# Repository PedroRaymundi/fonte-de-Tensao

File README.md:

# Fonte de Tensão
O objetivo final desse projeto é criar uma fonte de tensão com uma entrada de 127V AC 
e saída variável entre 3V e 12V com corrente contínua e 100mA

## Materiais
Materiais|Especificações|Preço
---------|--------------|-----
Transformador|16V 1A|+-R$50
Potenciômetro|2KΩ|+-R$1,04
Diodo (4x)|400V 3A|+-R$1,00
Capacitor|470uF 100V|+-R$3,13
Diodo Zener|13V (1W)|+-R$0,19
Resistor 1|220Ω (1W)|+-R$0,12
Resistor 2|820Ω (2W)|+-R$0,22
Transistor NPN|16V 1A|+-R$1,00

OBS: Alguns dos componentes podem ser encontrados por preços melhores e também podem ser substituídos por outros a fim de manter uma corrente mais estável. A escolha de diversos dos componentes utilizados nesse projeto foram a disponibilidade. Por exemplo: o transformador de 16V não é tão adequado quanto um de 20V para cima, entretanto só havia esse transformador a venda localmente quando o projeto foi iniciado.

## Projeto
Passo a passo de como montar o projeto e resumo da função de cada componente:
* #### Transformador:
    O transformador é conectado diretamente na tomada a fim de reduzir a corrente e a voltagem padrão da tomada para 16V e 1A. O objetivo disso é deixar mais fácil trabalhar com o sistema já que agora é possível utilizar componentes eletrônicos mais baratos que só precisam aguentar os 16V no lugar dos 127V. Além disso, também aproxima do resultado final desejado para o projeto e deixa o trabalho com o circuito mais seguro.
* #### Diodos:
    Antes de conectar os diodos ao circuito é necessário fazer uma ponte de diodos. Para isso é preciso pegar os quadro diodos e juntá-los seguindo o exemplo das fotos abaixo. Isso é feito porque o diodo só permite a passagem da corrente em uma direção (no caso do projeto seria a direção da flecha e, nos diodos reais, é a direção que vai da parte preta para a faixa cinza no diodo) e, com essa ponte montada, podemos utilizar os dois sentidos da corrente alternada que vai sair do transformador. Por esse motivo, conectaremos as pontas 1 e 2 (olhar desenho abaixo) do diodo no transformador.

* #### Capacitor:
    O capacitor serve para suprir a corrente energética enquanto a corrente da tomada está na inversão de fase e assim ajuda o circuito a manter uma corrente mais linear em todos os períodos. A partir desse momento é preciso tomar cuidado com a parte positiva e negativa do circuito, já que a ponte de diodos faz com que a corrente sempre saia do ponto 3 para o ponto 4. Por isso, é preciso conectar a parte positiva do capacitor em paralelo com a saída 3 e a parte negativa do capacitor com o ponto 4.
* #### Resistor 220Ω e diodo zener:
    O diodo zener serve apenas para limitar a voltagem (nesse caso em 13V), portanto, não há necessidade de passar muita corrente por ele, por esse motivo o resistor de 220Ω é colocado em série ao zener.
* #### Resitor 820Ω e potenciômetro:
    Para regular a voltagem entre 3V e 12V é usado o potenciômetro em série com o resistor de 820Ω, o resistor serve para limitar a voltagem mínima em 3V. Esse sistema é conectado entre o resistor de 220Ω e o diodo zener, seguindo o esquema a seguir:

* #### Transistor NPN:
    Para o transistor funcionar ele precisa de aproximadamente 0,7V do circuito, transformando assim os 13V (que haviam sido regulados pelo zener) em 12,3V, deixando quase que exatamente o que era pedido para o projeto. O seu funcionamento gira em torno justamente dessa necessidade de haver uma dirferança entre as voltagens, ou seja, o transistor interrompe a energia quando a voltagem começa a subir para além do que passa em sua base, e após isso acontecer, a voltagem diminui até ficar menor do que a que passa pela base, ligando novamente o transistor e voltando a passar a voltagem previamente regulada.

* #### Resultado final:
    
    OBS: o resistor de 120Ω 

    [projeto final](http://tinyurl.com/ycepgu2t)

## Soluções para problemas
Já em simulações é perceptível 2 problemas no projeto que podem ser facilmente solucionáveis:
* Existe uma pequena variação na voltagem e corrente final. Sendo a variação máxima 0,728V e 8,498mA entre picos e vales de corrente;
* Uma quantidade de corrente considerável passa pelo diodo zener sem necessidade;

Consertar cada um dos problemas é relativamente simples. Para isso será necessário:
1. Para o primeiro problema:
    1. Um potenciômetro de 5K;
    2. Um resistor de 2.2K;
2. Para o segundo problema:
    1. Um transformador de aproximadamente 20V;
    2. Um resistor de 1.2K;

Dito isso, o ideal seria aplicar essas duas resoluções simultaneamente. Mas caso não seja possível aplicar apenas uma delas já é muito preferível do que manter como está.

#### Resolvendo o primeiro problema
Para diminuir essa variação de corrente e voltagem, é preciso simplesmente trocar o potenciômetro original (2K) pelo novo potenciômetro (5K). Além disso, o resistor que está em série com o potenciômetro (820Ω) deve ser trocado pelo novo (2,2K).

[simulação com a primeira solução](http://tinyurl.com/ycsxajha)

#### Resolvendo o segundo problema
Para parar a perda de corrente que passa pelo diodo zener basta trocar o transformador de 16V pelo de 20V e trocar o resistor de 220Ω pelo de 1,2K.

[simulação com a segunda solução](http://tinyurl.com/ycv6hq6u)

[simulação com as duas soluções](http://tinyurl.com/ybmaza7z)

## EAGLE
### Projeto esquemático

### Projeto PCB

## Feito por:
* Pedro Henrique Raymundi, nUSP: 11795634

[video com o projeto finalizado](https://youtu.be/qeKwLvBPG0Y)

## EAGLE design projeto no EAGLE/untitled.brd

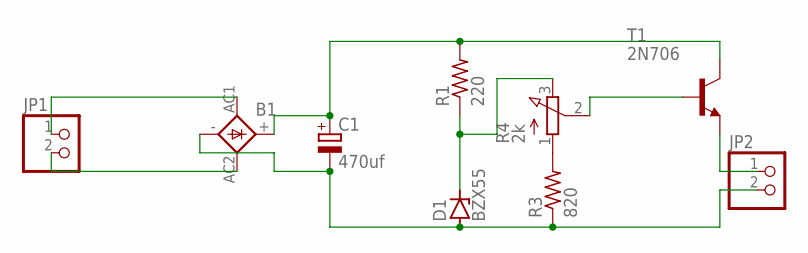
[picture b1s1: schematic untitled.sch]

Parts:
B1: 1KAB
C1: 470uf; E3,5-10
D1: BZX55; DO35Z10
JP1, JP2: PINHD-1X2; 1X02
R1: 220; 0309/12
R3: 820; 0309/12
R4: 2k; 3RP/1610N
T1: 2N706; TO18

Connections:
unnamed: R3.2, R4.1 (A)
unnamed: D1.C, R1.1, R4.3 (E)
unnamed: JP2.1, T1.1 (E)
unnamed: B1.AC1, JP1.1
unnamed: B1.AC2, JP1.2
unnamed: B1.+, C1.+, R1.2, T1.3 (C)
unnamed: B1.-, C1.-, D1.A, JP2.2, R3.1
unnamed: R4.2 (S), T1.2 (B)

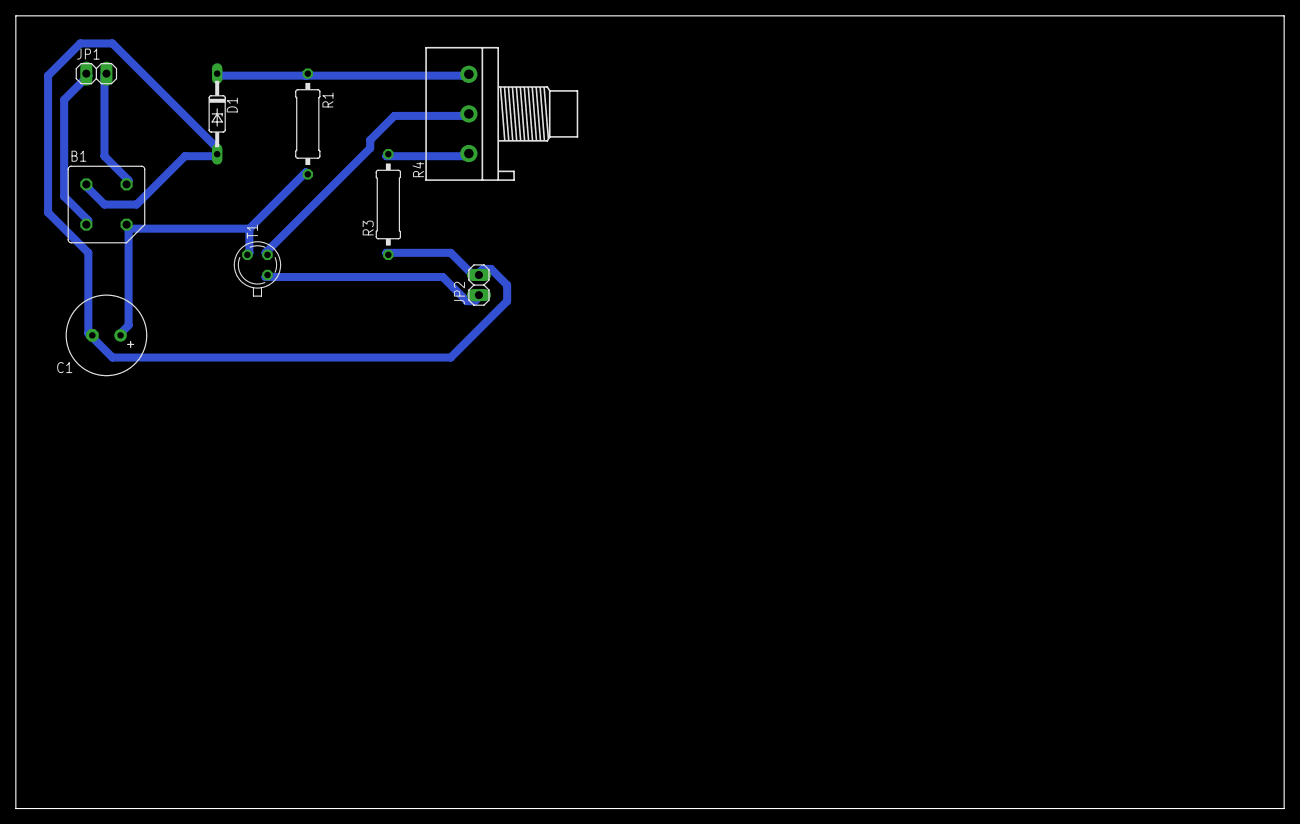
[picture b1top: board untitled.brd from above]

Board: 2 copper layers, 160.0 x 100.0 mm, 9 parts (0 on the bottom side), 8 nets.
